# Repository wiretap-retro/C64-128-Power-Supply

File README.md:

# C64/C128 Power Supply
This power supply is a simple design for the C64 or C128.

## Assembly
* Order the PCB from your choice of PCB fab. (JLCPCB, PCBway, OSH Park, etc.)
* Order the parts necessary as listed in the BOM. (The transformer can be substituted with a Talema 70041k if you can't find the Amgis)
* Solder the fuse holder, spade connectors, resistor, and pin header. Alternatively, an LED can be fit directly in place of the pin header.
* Solder the Meanwell 5V power supply and the transformer.
* Observe the jumper settings on the board near the 5V power LED. For 120V outlets, JP1 and JP2 require a wire link jumper. For 230V outlets, JP3 requires a wire link jumper.
* Grab a spare NEMA 1-15 or 5-15 cable and cut the female end off, stripping the wire insulation. Spare the ground cable if using a NEMA 5-15, as it isn't used. As for countries outside of North America, use an appropriate quality cable that matches your outlet.
* Install female spade connector fittings on your power plug wires that match the size of the male fittings on the PCB. They're found at any auto store.
* For the Commodore side of the connector, you can make your own cable with a 7-pin DIN, or cut the end off an old failed power supply. Follow the Commodore spec for your connections, using a multimeter for confirmation, as the wire colors may not always be correct.
* I don't have a case for this yet, but you can put it in a project box, mounted using the 4 holes provided on the PCB. If you're really inclined, make a 3D printed enclosure and please share files with the community. 
* Connect the power cables, insert the fuse, and start using it.

## Project Status
This power supply has been tested and confirmed working by numerous people. No issues have been reported.

## Other
This is an open source project. Feel free to do what you want with it.

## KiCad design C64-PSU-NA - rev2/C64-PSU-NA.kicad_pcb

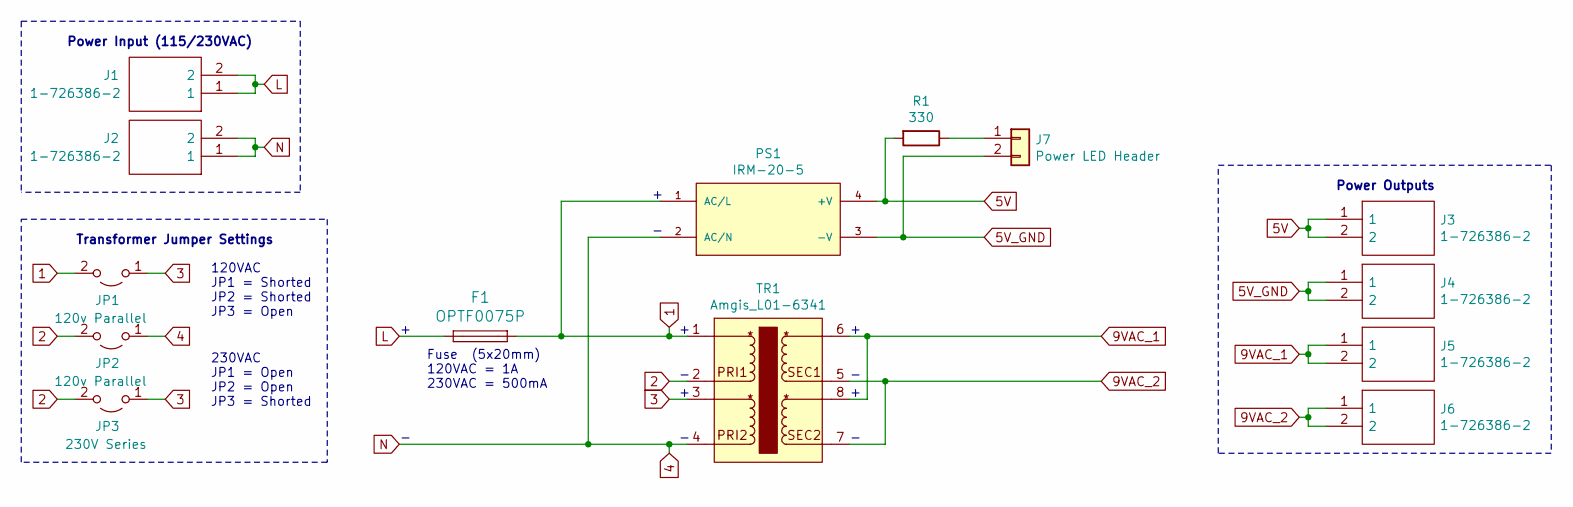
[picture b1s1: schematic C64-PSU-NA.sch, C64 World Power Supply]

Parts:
F1: OPTF0075P; 0PTF0075P
J1, J2, J3, J4, J5, J6: 1-726386-2; 17263862; Mouser Part Number 571-1-726386-2
J7: Power LED Header; PinHeader_1x02_P2.54mm_Vertical
JP1, JP2: 120v Parallel; SolderWire-0.75sqmm_1x02_P4.8mm_D1.25mm_OD2.3mm
JP3: 230V Series; SolderWire-0.75sqmm_1x02_P4.8mm_D1.25mm_OD2.3mm
PS1: IRM-20-5; CONV_IRM-20-5
R1: 330; R_Axial_DIN0204_L3.6mm_D1.6mm_P7.62mm_Horizontal
TR1: Amgis_L01-6341

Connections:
1: F1.2, JP1.2 (B), PS1.1 (AC/L), TR1.1
2: JP2.2 (B), JP3.2 (B), TR1.2
3: JP1.1 (A), JP3.1 (A), TR1.3
4: J2.1, J2.2, JP2.1 (A), PS1.2 (AC/N), TR1.4
5V: J3.1, J3.2, PS1.4 (+V), R1.2
5V_GND: J4.1, J4.2, J7.2, PS1.3 (-V)
9VAC_1: J5.1, J5.2, TR1.6, TR1.8
9VAC_2: J6.1, J6.2, TR1.5, TR1.7
L: F1.1, J1.1, J1.2
unnamed: J7.1, R1.1

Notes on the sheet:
Power Outputs
Power Input (115/230VAC)
Transformer Jumper Settings
120VAC JP1 = Shorted JP2 = Shorted JP3 = Open
230VAC JP1 = Open JP2 = Open JP3 = Shorted
Fuse (5x20mm) 120VAC = 1A 230VAC = 500mA

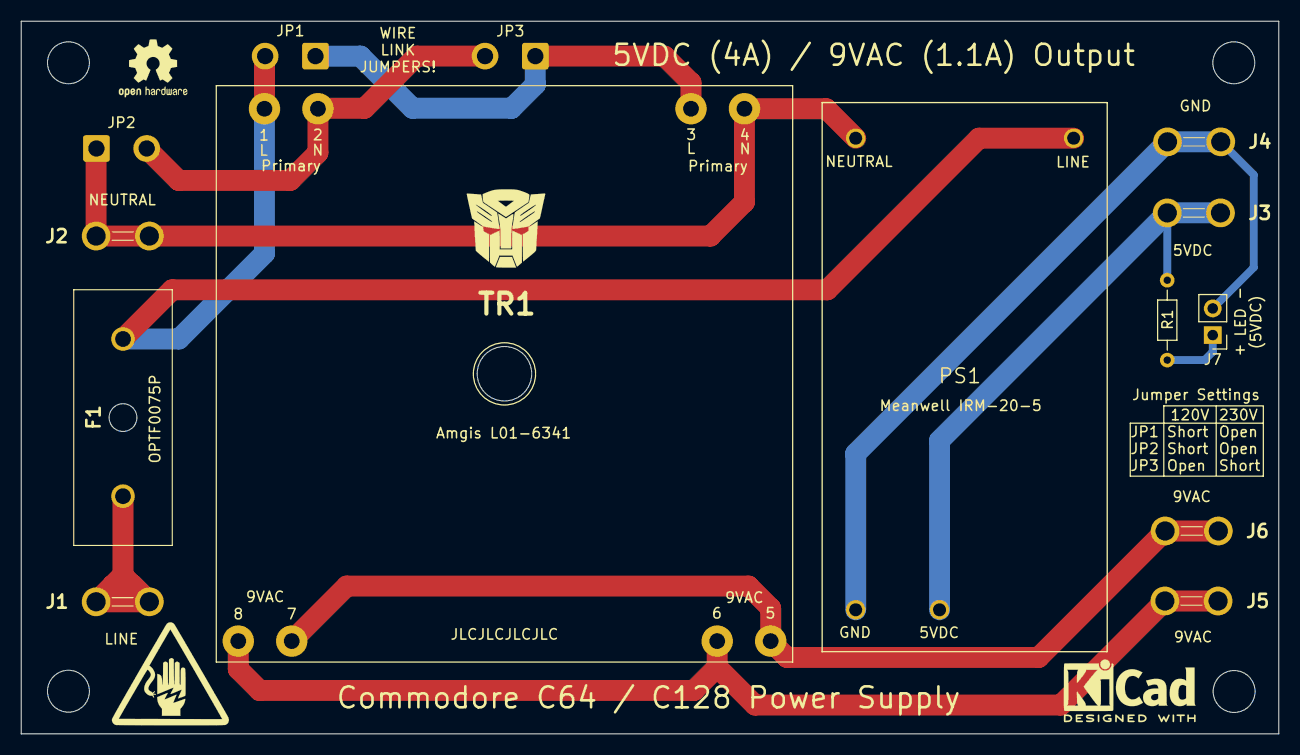
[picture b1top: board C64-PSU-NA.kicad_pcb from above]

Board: 2 copper layers, 120.0 x 68.0 mm, 14 parts (0 on the bottom side), 10 nets.
